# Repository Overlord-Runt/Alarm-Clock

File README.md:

# Curtain Manager Alarm Clock

Hello there. This project is an alarm clock that opens and closes my curtains for me because im too lazy to open them myself.

## Why I made this

This project came to mind after the 3rd day in a row I was unbothered to open my curtains in the morning and came home to a dark room.(darkness is scary)\
What? you expected some deep reason with an emotional backstory?\
Well too bad, everything I make is on a whim, boredom, or for the funnies.

## What this does

This is an alarm clock(shocker I know) that opens my curtains when it goes off.\
It has the following features:\

- Alarm Clock(You could have never guessed)
- Outside weather
- Inside weather
- Customisable Ring tone
- Opens Curtains for you

It is made up of 3 main sections:

- The Motor
- The Alarm body
- The Off Button

### The Motor
The motor I used for this is a NEMA17 Stepper and I designed a frame and gear for the motor to pulled my beaded curtain string.\
I chose this motor for 3 main reasons:

- The curtain is quite heavy and I dont believe a 5V motor could pull that much weight
- This stepper is quite cheap and I have used it before with it being simple to use.
- Steppers are cooler than 5V motors

I use a PCB to connect it to an A4988 stepper motor driver. This driver simplifies the firmware and wiring needed to control the motor.\
I also put a Buck Coverter inside because the stepper requires 12V whereas the alarm body needs 5, so the step down from a 12V power supply is what I felt would be easiest.\
If you want to use any other methods, it should be pretty easy to do.

### The Alarm Body

The alarm body features a 3d printed body, OLED SSD1306 128X64 Screen to view the current time, set alarm time, and view the weather. It also has 4 buttons that you czn use to change the time and do other cool programable things.

Inside there are

- 4 Buttons
- An SSD1306 OLED screen
- An ESP32
- An RTC
- 2 Buzzers
- A DHT22 sensor

The Alarm Body and the Motor are connected through a USBA-A cable as that allows for power transmission and for the 2 datalines for the stepper to transmit between the 2 modules in one clean cable.

### The Off Button

The off Button connects to the Alarm Body with wires and can be placed basically anywhere.\
I personally like to use a big red button but if you wish to use something else like a motion sensor, I have left the pins available to use so that it is possible to use either option with no change to the firmware.

Why no snooze button?

Snooze buttons are for losers. If your alarm goes off, get your ass out of bed.

## How to make it

Wow you also wanna make this. I am honoured to hear that.

First thing you wanna do is download the cad folder and get all those files printing.

This is the anoying part

I made this part to fit my own curtains. You will have to edit it to fit your own curtains. Everything else should be kept the same.

Order all the parts and the pcb. Once they arrive, you can get to soldering it all together. I will include photos of the finished version once I build it myself so you have a reference.

You need to put 3 heatsets per pcb and then 4 for the front panel of the Alarm Body.

The button connects via wires going through the back hole. the placement of the USBA hole is hopefully correct, If not, I can just change it.

After that you can flash the esp with firmware listed in the firmware folder(WIP FOR NOW) and screw everything in.

## Design files

Here are photos of the design files and models

\
\
\
\
\

# Bill Of Materials

List Of all materials needed to make this.

 - Nema17 Stepper Motor - x1 -  $13 - [source](https://www.omc-stepperonline.com/e-series-nema-17-bipolar-42ncm-59-49oz-in-1-5a-42x42x38mm-4-wires-w-1m-cable-connector-17he15-1504s)
 - Buzzer - x2
 - SSD1306 128X64 OLED display - X1 - $3.15 - Preowned
 - Buck Converter - X1 - $3.09 - [source](https://www.aliexpress.com/item/1005007259901753.html?spm=a2g0o.cart.0.0.3fb538daUB00x5&mp=1&pdp_npi=5%40dis%21AUD%21AUD%205.20%21AUD%204.89%21%21AUD%204.89%21%21%21%402101e9ec17487026778881064ecff3%2112000039979305524%21ct%21AU%216138339337%21%211%210)
 - RTC - X1 - $2.27 - [source](https://www.aliexpress.com/item/1005008172587774.html?spm=a2g0o.cart.0.0.3fb538daUB00x5&mp=1&pdp_npi=5%40dis%21AUD%21AUD%203.54%21AUD%203.54%21%21AUD%203.37%21%21%21%402101e9ec17487026778881064ecff3%2112000044177906467%21ct%21AU%216138339337%21%211%210)
 - ESP32-WROOM Dev Board - X1 - $4.24 - [source](https://www.aliexpress.com/item/1005006456519790.html?spm=a2g0o.cart.0.0.3fb538daUB00x5&mp=1&pdp_npi=5%40dis%21AUD%21AUD%2019.78%21AUD%206.61%21%21AUD%206.54%21%21%21%402101e9ec17487026778881064ecff3%2112000037265317361%21ct%21AU%216138339337%21%211%210)
 - PCB - X2 - $12.06 - JLCPCB
 - M3X05X06 Heatsets - X10 - $2.49 - [source](https://www.aliexpress.com/item/1005003582355741.html?spm=a2g0o.cart.0.0.3fb538daUB00x5&mp=1&pdp_npi=5%40dis%21AUD%21AUD%203.89%21AUD%203.89%21%21AUD%203.81%21%21%21%402101c59517487030715636687ef171%2112000026370649803%21ct%21AU%216138339337%21%211%210)
 - M3X6mm Screws - X14 - $1 - [source](https://www.aliexpress.com/item/32810852732.html?spm=a2g0o.cart.0.0.3fb538daUB00x5&mp=1&pdp_npi=5%40dis%21AUD%21AUD%202.32%21AUD%201.56%21%21AUD%201.48%21%21%21%402101e9ec17487026778881064ecff3%2112000037550700849%21ct%21AU%216138339337%21%211%210)
 - 12V Battery - X1 - $16.06 - [source](https://www.jaycar.com.au/12v-2-2ah-sla-battery/p/SB2482)
 - DHT22 Sensor - X1 - $1.73 - [source](https://www.aliexpress.com/item/32759901711.html?spm=a2g0o.cart.0.0.3fb538daUB00x5&mp=1&pdp_npi=5%40dis%21AUD%21AUD%202.69%21AUD%202.69%21%21AUD%202.69%21%21%21%402101e9ec17487026778881064ecff3%2162102476019%21ct%21AU%216138339337%21%211%210)
 - A4988 Motor Driver - X1 - $2.12 - [source](https://www.aliexpress.com/item/1005001771907921.html?spm=a2g0o.productlist.main.7.651fvWRBvWRBe0&algo_pvid=2133a30e-defa-4302-9858-dbc2495931f1&algo_exp_id=2133a30e-defa-4302-9858-dbc2495931f1-6&pdp_ext_f=%7B%22order%22%3A%22398%22%2C%22eval%22%3A%221%22%7D&pdp_npi=4%40dis%21AUD%214.89%214.89%21%21%213.10%213.10%21%402103010b17487023403607387e16b7%2112000046636839301%21sea%21AU%216138339337%21ABX&curPageLogUid=J6WxTjF3i9rx&utparam-url=scene%3Asearch%7Cquery_from%3A)
 - DS1095 USBA female port - X2 - $1.38 - [source](https://www.aliexpress.com/item/1005007822597305.html?spm=a2g0o.productlist.main.10.5df02562xE320M&algo_pvid=dd419a23-631b-4b7b-a0fb-6edaa9da48a0&algo_exp_id=dd419a23-631b-4b7b-a0fb-6edaa9da48a0-9&pdp_ext_f=%7B%22order%22%3A%221101%22%2C%22eval%22%3A%221%22%2C%22orig_sl_item_id%22%3A%221005007822597305%22%2C%22orig_item_id%22%3A%221005007077769791%22%7D&pdp_npi=4%40dis%21AUD%213.86%211.85%21%21%2117.58%218.44%21%402101eac917487032447777243efaea%2112000042331903916%21sea%21AU%216138339337%21ABX&curPageLogUid=2g05IbKQywTu&utparam-url=scene%3Asearch%7Cquery_from%3A)
 - USBA-A Cable - X1 - $1.29 - [source](https://www.aliexpress.com/item/1005007441805917.html?spm=a2g0o.productlist.main.3.296elc0wlc0w0u&algo_pvid=5a890205-65cb-4692-ae3d-cc6aeffe4b49&algo_exp_id=5a890205-65cb-4692-ae3d-cc6aeffe4b49-2&pdp_ext_f=%7B%22order%22%3A%224813%22%2C%22eval%22%3A%221%22%7D&pdp_npi=4%40dis%21AUD%212.04%211.56%21%21%219.30%217.11%21%4021030ea417487034244743454ed487%2112000040770581049%21sea%21AU%216138339337%21ABX&curPageLogUid=J4UnCQ3jA9Ju&utparam-url=scene%3Asearch%7Cquery_from%3A)
 - 6mm Buttons - X4
 - Wire - 1m

Total: $56.01

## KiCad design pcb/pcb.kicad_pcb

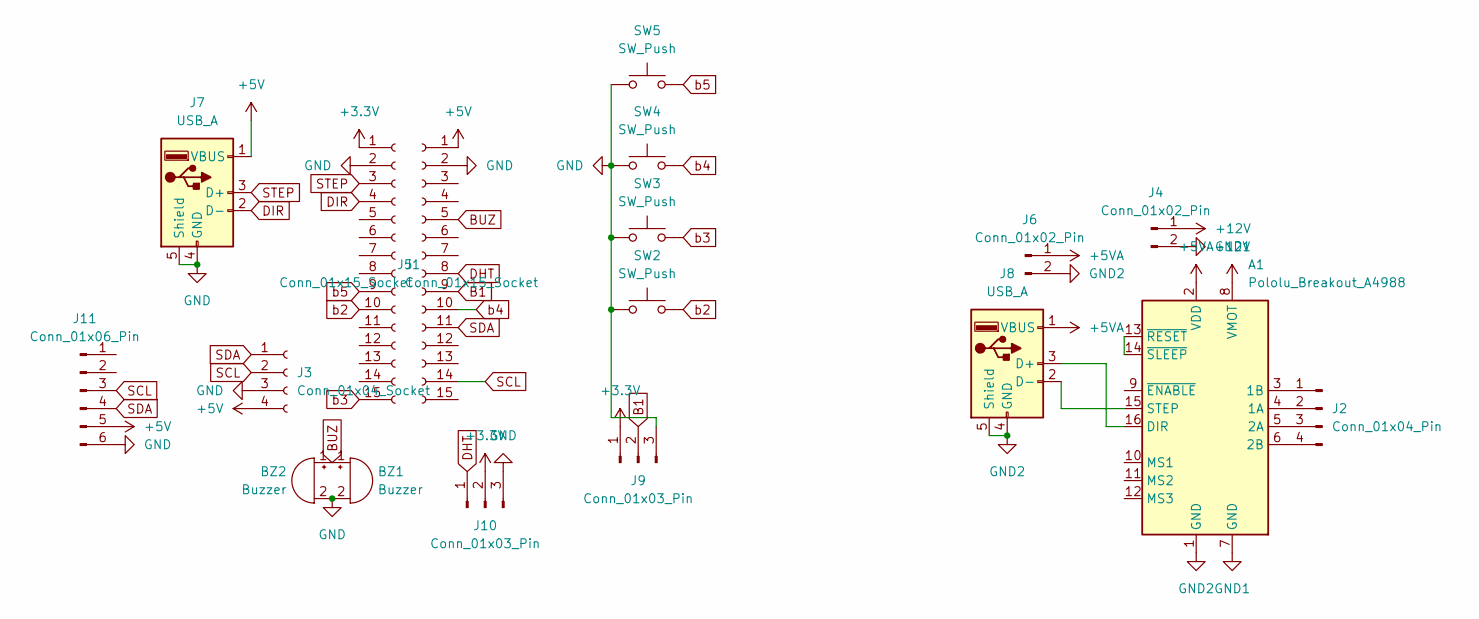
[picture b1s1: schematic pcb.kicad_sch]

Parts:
A1: Pololu_Breakout_A4988; Pololu_Breakout-16_15.2x20.3mm
BZ1, BZ2: Buzzer; Indicator_PUI_AI-1440-TWT-24V-2-R
J1, J5: Conn_01x15_Socket; PinHeader_1x15_P2.54mm_Vertical
J2: Conn_01x04_Pin; PinHeader_1x04_P2.54mm_Vertical
J3: Conn_01x04_Socket; PinSocket_1x04_P2.54mm_Vertical
J4, J6: Conn_01x02_Pin; PinHeader_1x02_P2.54mm_Vertical
J7, J8: USB_A; USB_A_Connfly_DS1095
J9, J10: Conn_01x03_Pin; PinHeader_1x03_P2.54mm_Vertical
J11: Conn_01x06_Pin; PinHeader_1x06_P2.54mm_Vertical
SW2, SW3, SW4, SW5: SW_Push; Button-6mm-2pin-tht

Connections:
+3.3V: J1.1, J9.1, J10.2
+5V: J3.4, J5.1, J7.1 (VBUS), J11.5
+5VA: A1.2 (VDD), J6.1, J8.1 (VBUS)
+12V: A1.8 (VMOT), J4.1
B1: J5.9, J9.2
BUZ: BZ1.1 (+), BZ2.1 (+), J5.5
DHT: J5.8, J10.1
DIR: J1.4, J7.2 (D-)
GND: BZ1.2 (-), BZ2.2 (-), J1.2, J3.3, J5.2, J7.4 (GND), J7.5 (Shield), J9.3, J10.3, J11.6, SW2.1, SW3.1, SW4.1, SW5.1
GND1: A1.7 (GND), J4.2
GND2: A1.1 (GND), J6.2, J8.4 (GND), J8.5 (Shield)
unnamed: A1.4 (1A), J2.2
unnamed: A1.3 (1B), J2.1
unnamed: A1.5 (2A), J2.3
unnamed: A1.6 (2B), J2.4
unnamed: A1.16 (DIR), J8.3 (D+)
unnamed: A1.15 (STEP), J8.2 (D-)
unnamed: A1.13 (~RESET), A1.14 (~SLEEP)
SCL: J3.2, J5.14, J11.3
SDA: J3.1, J5.11, J11.4
STEP: J1.3, J7.3 (D+)
b2: J1.10, SW2.2
b3: J1.15, SW3.2
b4: J5.10, SW4.2
b5: J1.9, SW5.2

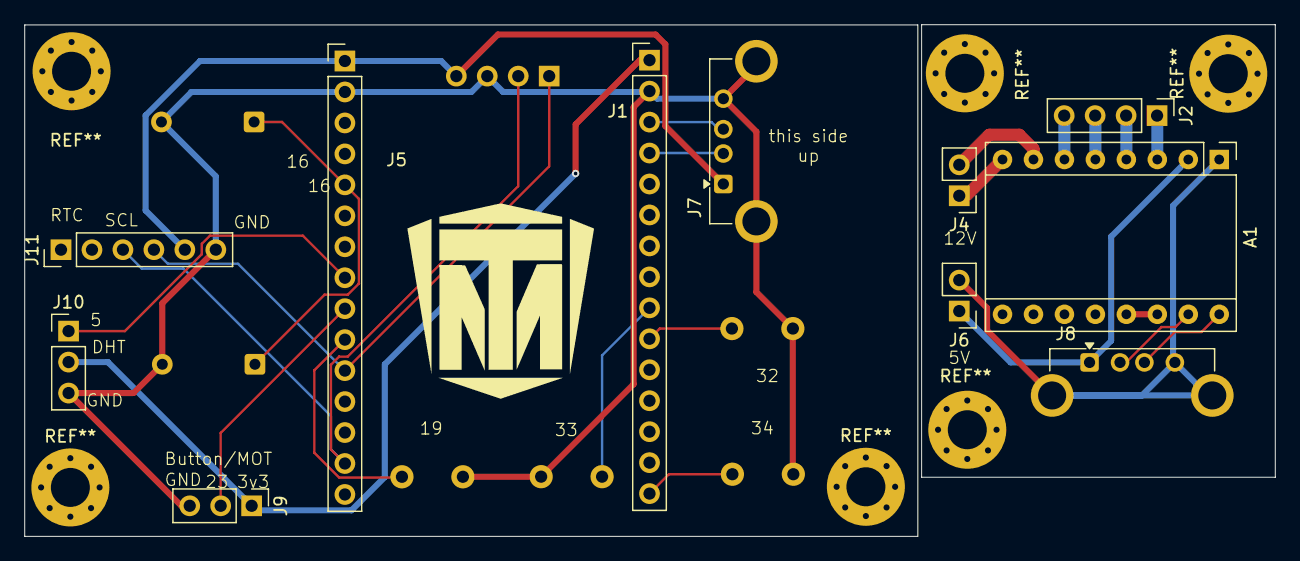
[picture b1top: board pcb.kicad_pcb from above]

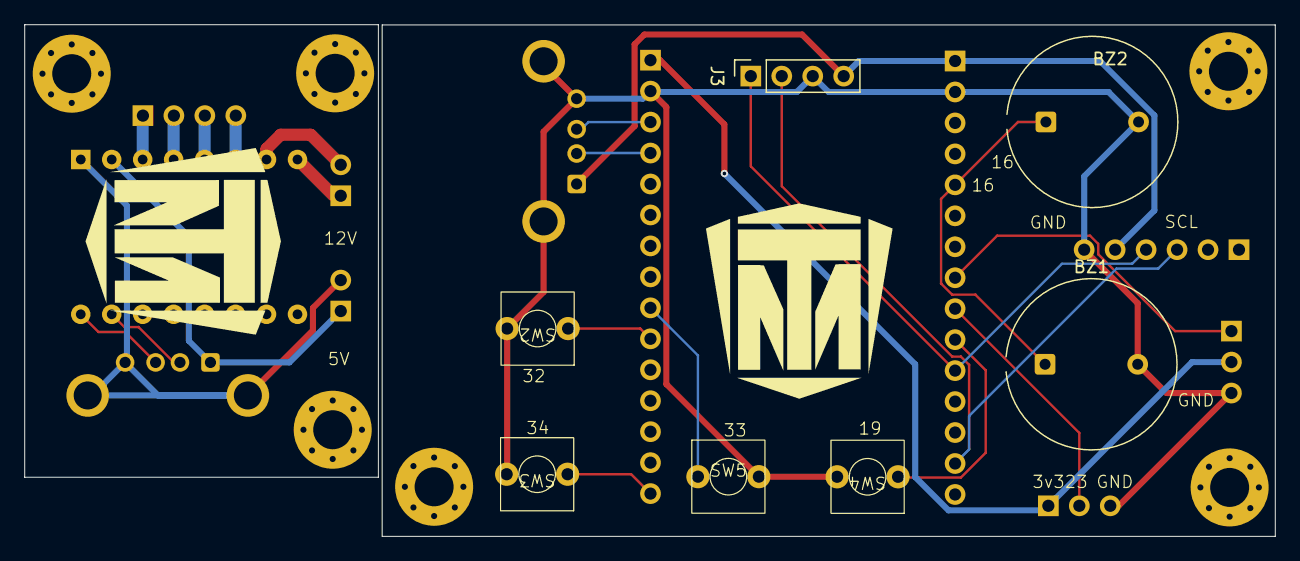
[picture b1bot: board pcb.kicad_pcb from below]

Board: 2 copper layers, 102.6 x 42.0 mm, 18 parts (7 on the bottom side), 25 nets.

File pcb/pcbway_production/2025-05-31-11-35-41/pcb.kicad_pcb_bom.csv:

Designator,Quantity,Value,Footprint,Package,MPN,DNP,Mount_Type,Description
A1,1,Pololu_Breakout_A4988,Pololu_Breakout-16_15.2x20.3mm,,,,tht,"Pololu Breakout Board, Stepper Driver A4988"
"BZ1, BZ2",2,Buzzer,Indicator_PUI_AI-1440-TWT-24V-2-R,,,,tht,"Buzzer, polarized"
"J1, J5",2,Conn_01x15_Socket,PinHeader_1x15_P2.54mm_Vertical,,,,tht,"Generic connector, single row, 01x15, script generated"
"J10, J9",2,Conn_01x03_Pin,PinHeader_1x03_P2.54mm_Vertical,,,,tht,"Generic connector, single row, 01x03, script generated"
J11,1,Conn_01x06_Pin,PinHeader_1x06_P2.54mm_Vertical,,,,tht,"Generic connector, single row, 01x06, script generated"
J2,1,Conn_01x04_Pin,PinHeader_1x04_P2.54mm_Vertical,,,,tht,"Generic connector, single row, 01x04, script generated"
J3,1,Conn_01x04_Socket,PinSocket_1x04_P2.54mm_Vertical,,,,tht,"Generic connector, single row, 01x04, script generated"
"J4, J6",2,Conn_01x02_Pin,PinHeader_1x02_P2.54mm_Vertical,,,,tht,"Generic connector, single row, 01x02, script generated"
"J7, J8",2,USB_A,USB_A_Connfly_DS1095,,,,tht,USB Type A connector
"SW2, SW3, SW4, SW5",4,SW_Push,Button-6mm-2pin-tht,,,,smt,"Push button switch, generic, two pins"

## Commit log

2025-05-31 Rename coca cola. don't forget the ice... [kAGRRs64oD8].mp4 to cocacola.mp4
2025-05-31 Update JOURNAL.md again
